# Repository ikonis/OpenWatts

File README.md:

# OpenWatts

OpenWatts is a crank-mounted, single-sided cycling power meter built around an
ESP32-C3. A bonded strain-gauge bridge and HX711 measure crank torque, while an
LSM6DS3 IMU provides cadence and motion wake. Firmware publishes standard BLE
Cycling Power Service data and includes calibration, ride recording, battery
management, OTA updates, a responsive WebUI, and optional MQTT/Home Assistant
reporting.

The board in this repository is **OpenWatts RevA**, the same revision currently
installed on my bike. It has been calibrated and used with:

`OpenWatts --BLE CPS--> SmartSpin2K --> MyWhoosh`

## Features

- calibrated strain/HX711 torque and IMU cadence
- conventional single-sided total-power estimate: calibrated left-crank power
  doubled once for BLE Cycling Power, ride summaries, and road estimates
- Normal and Maintenance operating modes
- motion wake and battery-conscious light sleep
- guided Bench Calibration plus runtime Ride Zero
- phone-first live ride dashboard with read-only SmartSpin2K LAN data
- Last Ride statistics and estimated road distance/speed
- web OTA over USB or while working in Maintenance mode
- MQTT battery/ride reports and Home Assistant discovery

## Hardware

- [KiCad schematic](OpenWatts.kicad_sch)
- [KiCad PCB](OpenWatts.kicad_pcb)
- [BOM](HARDWARE_BOM.md)
- [schematic and board images](docs/hardware/)
- [PCBWay manufacturing files](fab/pcbway-2026-07-06/)
- [final-fit RevA board and case assembly](mechanical/OpenWatts_RevA_Enclosed_Assembly.step)
- [installation checklist](docs/INSTALLATION_CHECKLIST.md)
- [calibration guide](docs/CALIBRATION.md)

The checked-in KiCad PCB is the board that was manufactured. Notes from building
and using it are kept separately in [REV_B_NOTES.md](REV_B_NOTES.md) in case I
ever make another revision.

## Firmware

Firmware source and build instructions are in
[firmware/README.md](firmware/README.md). Start with the
[documentation index](docs/README.md) for setup, calibration, architecture,
Home Assistant, and validation notes.

## Notes

- RevA uses light sleep because its IMU interrupt is not connected to an
  ESP32-C3 deep-sleep-capable GPIO.
- Battery percentage is estimated from voltage, so the voltage reading is the
  useful number when accuracy matters.
- MQTT uses unauthenticated plain TCP on a trusted LAN.
- Road speed and distance are modeled estimates, not wheel/GPS measurements.
- OpenWatts measures left-crank torque only. It assumes approximately equal
  left/right contribution when estimating total cycling power; cadence itself
  is measured directly and is never doubled.

## License

OpenWatts is open hardware and open-source software:

- Hardware design, fabrication, and mechanical files:
  [CERN-OHL-P-2.0](LICENSES/CERN-OHL-P-2.0.txt)
- Firmware, WebUI, scripts, and documentation: [MIT](LICENSES/MIT.txt)

See [LICENSE.md](LICENSE.md) for the exact scope and warranty notice.

OpenWatts is provided as-is, without warranty. Building or using it is entirely
at your own risk. I am not responsible for injury, damaged equipment, battery
problems, inaccurate measurements, data loss, or other losses resulting from
its construction or use.

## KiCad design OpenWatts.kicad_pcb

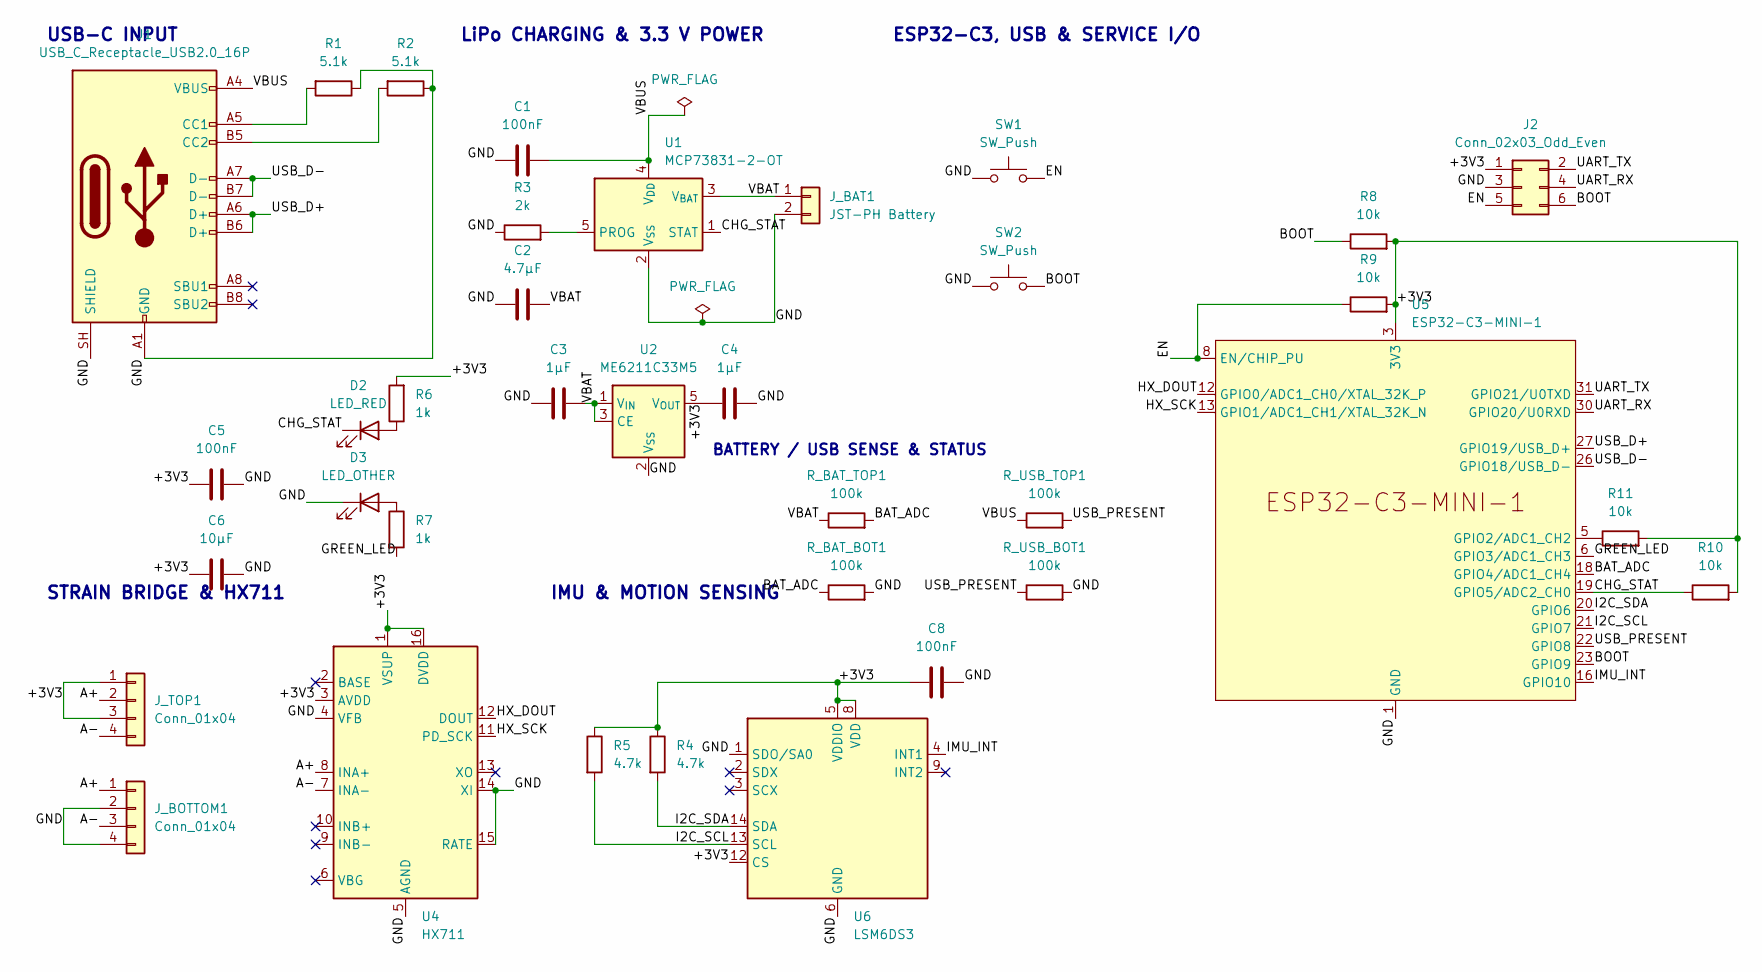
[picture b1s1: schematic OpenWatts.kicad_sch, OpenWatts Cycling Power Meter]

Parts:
C1, C5, C8: 100nF; C_0603_1608Metric
C2: 4.7µF; C_0603_1608Metric
C3, C4: 1µF; C_0603_1608Metric
C6: 10µF; C_0603_1608Metric
D2: LED_RED; LED_0603_1608Metric
D3: LED_OTHER; LED_0603_1608Metric
J1: USB_C_Receptacle_USB2.0_16P; USB_C_Receptacle_HRO_TYPE-C-31-M-12
J2: Conn_02x03_Odd_Even; PinHeader_2x03_P2.54mm_Vertical
J_BAT1: JST-PH Battery; JST_PH_B2B-PH-K_1x02_P2.00mm_Vertical
J_BOTTOM1: Conn_01x04; JST_XH_S4B-XH-A_1x04_P2.50mm_Horizontal
J_TOP1: Conn_01x04; JST_XH_S4B-XH-A_1x04_P2.50mm_Horizontal
R1, R2: 5.1k; R_0603_1608Metric
R3: 2k; R_0603_1608Metric
R4, R5: 4.7k; R_0603_1608Metric
R6, R7: 1k; R_0603_1608Metric
R8, R9, R10, R11: 10k; R_0603_1608Metric
R_BAT_BOT1: 100k; R_0603_1608Metric
R_BAT_TOP1: 100k; R_0603_1608Metric
R_USB_BOT1: 100k; R_0603_1608Metric
R_USB_TOP1: 100k; R_0603_1608Metric
SW1, SW2: SW_Push; SW_SPST_EVQP2_MiddlePushTravel_H2.5mm
U1: MCP73831-2-OT; SOT-23-5
U2: ME6211C33M5; SOT-23-5
U4: HX711; SOIC-16_3.9x9.9mm_P1.27mm
U5: ESP32-C3-MINI-1
U6: LSM6DS3; LGA-14_3x2.5mm_P0.5mm_LayoutBorder3x4y

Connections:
/+3V3: C4.1, C5.1, C6.1, C8.1, J2.1, J_TOP1.1, J_TOP1.3, R4.1, R5.1, R6.2, R8.2, R9.2, R10.2, R11.2, U2.5 (V_{OUT}), U4.1 (VSUP), U4.3 (AVDD), U4.16 (DVDD), U5.3 (3V3), U6.5 (VDDIO), U6.8 (VDD), U6.12 (CS)
/A+: J_BOTTOM1.1, J_TOP1.2, U4.8 (INA+)
/A-: J_BOTTOM1.3, J_TOP1.4, U4.7 (INA-)
/BAT_ADC: R_BAT_BOT1.1, R_BAT_TOP1.2, U5.18 (GPIO4/ADC1_CH4)
/BOOT: J2.6, R8.1, SW2.2, U5.23 (GPIO9)
/CHG_STAT: D2.1 (K), R10.1, U1.1 (STAT), U5.19 (GPIO5/ADC2_CH0)
/EN: J2.5, R9.1, SW1.2, U5.8 (EN/CHIP_PU)
/GND: C1.1, C2.2, C3.1, C4.2, C5.2, C6.2, C8.2, D3.1 (K), J1.A1 (GND), J1.A12 (GND), J1.B1 (GND), J1.B12 (GND), J1.SH (SHIELD), J2.3, J_BAT1.2, J_BOTTOM1.2, J_BOTTOM1.4, R1.1, R2.1, R3.1, R_BAT_BOT1.2, R_USB_BOT1.2, SW1.1, SW2.1, U1.2 (V_{SS}), U2.2 (V_{SS}), U4.4 (VFB), U4.5 (AGND), U4.14 (XI), U4.15 (RATE), U5.1 (GND), U5.2 (GND), U5.11 (GND), U5.14 (GND), U5.36 (GND), U5.37 (GND), U5.38 (GND), U5.39 (GND), U5.40 (GND), U5.41 (GND), U5.42 (GND), U5.43 (GND), U5.44 (GND), U5.45 (GND), U5.46 (GND), U5.47 (GND), U5.48 (GND), U5.49 (GND), U5.50 (GND), U5.51 (GND), U5.52 (GND), U5.53 (GND), U6.1 (SDO/SA0), U6.6 (GND), U6.7 (GND)
/GREEN_LED: R7.2, U5.6 (GPIO3/ADC1_CH3)
/HX_DOUT: U4.12 (DOUT), U5.12 (GPIO0/ADC1_CH0/XTAL_32K_P)
/HX_SCK: U4.11 (PD_SCK), U5.13 (GPIO1/ADC1_CH1/XTAL_32K_N)
/I2C_SCL: R5.2, U5.21 (GPIO7), U6.13 (SCL)
/I2C_SDA: R4.2, U5.20 (GPIO6), U6.14 (SDA)
/IMU_INT: U5.16 (GPIO10), U6.4 (INT1)
/UART_RX: J2.4, U5.30 (GPIO20/U0RXD)
/UART_TX: J2.2, U5.31 (GPIO21/U0TXD)
/USB_D+: J1.A6 (D+), J1.B6 (D+), U5.27 (GPIO19/USB_D+)
/USB_D-: J1.A7 (D-), J1.B7 (D-), U5.26 (GPIO18/USB_D-)
/USB_PRESENT: R_USB_BOT1.1, R_USB_TOP1.2, U5.22 (GPIO8)
/VBAT: C2.1, C3.2, J_BAT1.1, R_BAT_TOP1.1, U1.3 (V_{BAT}), U2.1 (V_{IN}), U2.3 (CE)
/VBUS: C1.2, J1.A4 (VBUS), J1.A9 (VBUS), J1.B4 (VBUS), J1.B9 (VBUS), R_USB_TOP1.1, U1.4 (V_{DD})
unnamed: D2.2 (A), R6.1
unnamed: D3.2 (A), R7.1
unnamed: J1.A5 (CC1), R1.2
unnamed: J1.B5 (CC2), R2.2
unnamed: R3.2, U1.5 (PROG)
unnamed: R11.1, U5.5 (GPIO2/ADC1_CH2)

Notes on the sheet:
USB-C INPUT
LiPo CHARGING & 3.3 V POWER
ESP32-C3, USB & SERVICE I/O
STRAIN BRIDGE & HX711
IMU & MOTION SENSING
BATTERY / USB SENSE & STATUS

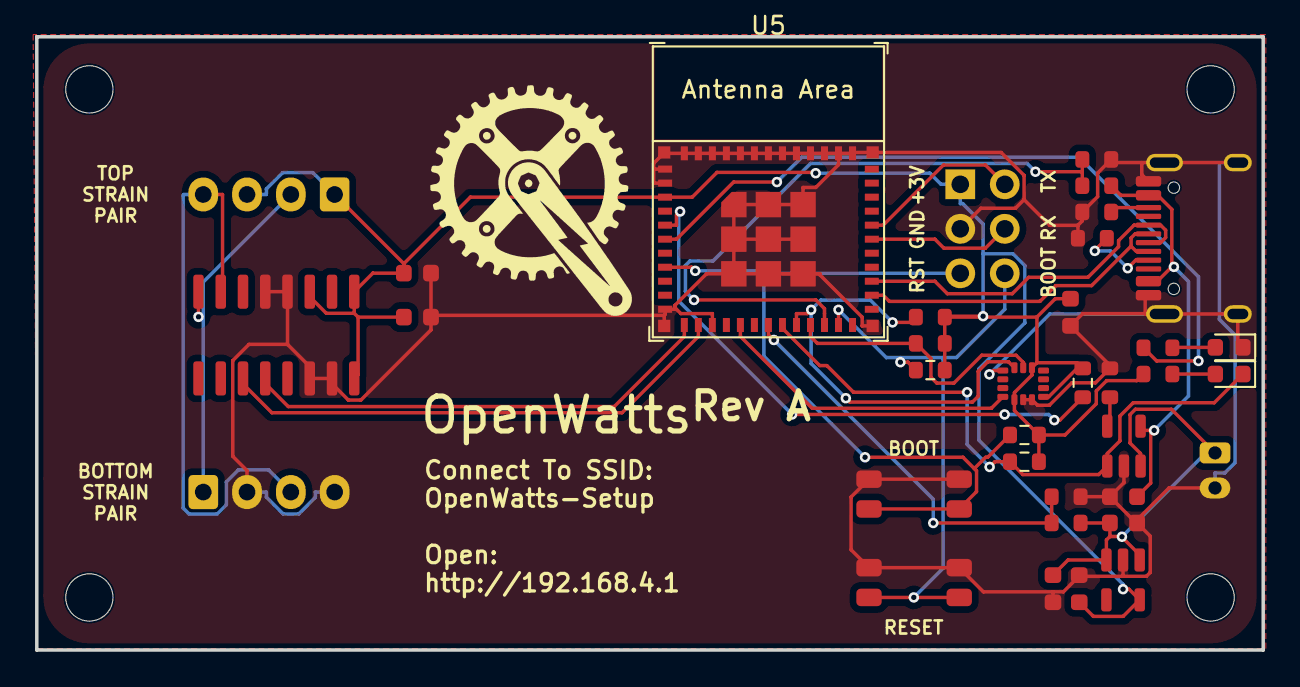
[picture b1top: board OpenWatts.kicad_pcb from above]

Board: 2 copper layers, 70.0 x 35.0 mm, 40 parts (0 on the bottom side), 27 nets.

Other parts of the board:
H1, H2, H3, H4: MountingHole_2.7mm_M2.5

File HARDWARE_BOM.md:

# OpenWatts RevA hardware BOM

This BOM covers the manufactured RevA board. It is based on the checked-in
schematic, PCB, and July 6 PCBWay assembly files. Where only a value or package
is known, that is all that is listed.

## MCU and sensors

| References | Qty | Component | Exact value / part | Package / footprint | Purpose |
|---|---:|---|---|---|---|
| U5 | 1 | Wi-Fi/BLE MCU module | ESP32-C3-MINI-1 | Espressif ESP32-C3-MINI-1 | Firmware, BLE CPS, Wi-Fi/WebUI, power policy |
| U6 | 1 | 6-axis IMU | LSM6DS3 | LGA-14, 3 x 2.5 mm, 0.5 mm pitch | Cadence, motion detection, wake interrupt |
| U4 | 1 | 24-bit bridge ADC | HX711 | SOIC-16, 3.9 x 9.9 mm, 1.27 mm pitch | Strain-bridge measurement |

## Power and charging

| References | Qty | Component | Exact value / part | Package / footprint | Purpose |
|---|---:|---|---|---|---|
| U1 | 1 | Single-cell LiPo charger | MCP73831-2-OT | SOT-23-5 | 4.20 V linear charging and charge-status output |
| U2 | 1 | 3.3 V LDO | ME6211C33M5 | SOT-23-5 | Regulated 3.3 V rail |
| R3 | 1 | Resistor | 2 kOhm | 0603 | Charger programming/support |
| C2 | 1 | Capacitor | 4.7 uF | 0603 | Power filtering |
| C3, C4 | 2 | Capacitor | 1 uF | 0603 | Power filtering |
| C6 | 1 | Capacitor | 10 uF | 0603 | Bulk rail filtering |

## Strain measurement and sensors

| References | Qty | Component | Exact value / part | Package / footprint | Purpose |
|---|---:|---|---|---|---|
| C1, C5, C8 | 3 | Capacitor | 100 nF | 0603 | Local decoupling |
| R4, R5 | 2 | Resistor | 4.7 kOhm | 0603 | IMU I2C pull-ups |
| J_TOP1, J_BOTTOM1 | 2 | 4-pin right-angle connector | JST XH S4B-XH-A family footprint | 1 x 4, 2.50 mm pitch | Top/bottom strain-pair connections |

## USB, programming, controls, and indication

| References | Qty | Component | Exact value / part | Package / footprint | Purpose |
|---|---:|---|---|---|---|
| J1 | 1 | USB-C USB 2.0 receptacle | HRO TYPE-C-31-M-12 footprint | 16-pin SMT/TH shield | USB power, native USB data, firmware service |
| R1, R2 | 2 | USB-C CC resistor | 5.1 kOhm | 0603 | Sink-role CC pull-downs |
| J2 | 1 | Service header | Generic 2 x 3 | 2.54 mm vertical | 3.3 V, GND, UART TX/RX, EN, BOOT |
| SW1, SW2 | 2 | Momentary push button | EVQP2-style middle-push footprint | SMD, H2.5 mm | EN/reset and GPIO9 boot controls |
| D2, D3 | 2 | Indicator LED | Color/order defined by assembled board | 0603 | Charge and MCU-controlled status indication |
| R6, R7 | 2 | LED resistor | 1 kOhm | 0603 | LED current limiting |
| R8-R11 | 4 | Resistor | 10 kOhm | 0603 | MCU boot/reset and signal biasing |

## Battery and USB sensing

| References | Qty | Component | Exact value / part | Package / footprint | Purpose |
|---|---:|---|---|---|---|
| R_BAT_TOP1, R_BAT_BOT1 | 2 | Resistor | 100 kOhm | 0603 | Battery-voltage ADC divider |
| R_USB_TOP1, R_USB_BOT1 | 2 | Resistor | 100 kOhm | 0603 | USB-present sensing divider |
| J_BAT1 | 1 | Battery connector | JST-PH B2B-PH-K family footprint | 1 x 2, 2.00 mm vertical | Single-cell LiPo connection |

## External build materials

These are required for the complete device but are not PCB assembly items.
Where the repository does not establish an exact purchasable part, none is
invented here.

| Item | Known requirement | Notes |
|---|---|---|
| Strain gauges | Bonded foil gauges wired as the installed crank bridge | Exact gauge manufacturer/part is not established in the repository |
| Battery | Protected single-cell LiPo compatible with the JST-PH connection and enclosure | Capacity and exact supplier are build-specific |
| Crank | Left crank prepared for bonded gauges and enclosure mounting | Calibration is installation-specific |
| Enclosure | See `mechanical/OpenWatts_RevA_Enclosed_Assembly.step` for the fitted board-and-case assembly | Verify print/material/fastening for the actual installation |
| Wiring/connectors | Mating JST-PH battery and JST-XH strain harnesses | Observe actual polarity and connector orientation |
| Gauge adhesive/protection | Suitable strain-gauge bonding and environmental protection system | Exact product is not established in the repository |

## About the generated BOM

`OpenWatts.kicad_pcb` and `fab/pcbway-2026-07-06/` describe the manufactured
geometry. `production/bom.csv` is a generated engineering export; this document
corrects its misleading per-reference LED quantities by listing D2 and D3 once
each.
